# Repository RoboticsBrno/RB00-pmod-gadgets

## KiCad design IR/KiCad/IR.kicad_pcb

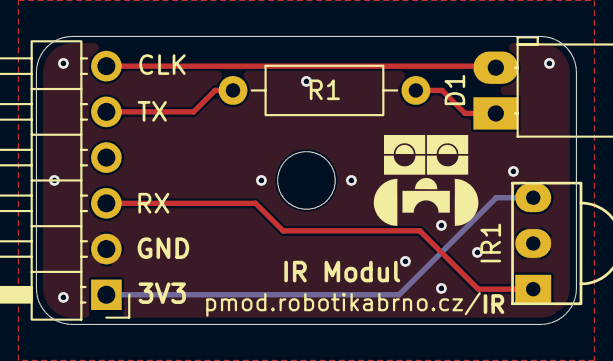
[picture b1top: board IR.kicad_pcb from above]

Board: 2 copper layers, 30.0 x 16.0 mm, 5 parts (0 on the bottom side), 6 nets.

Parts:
D1: IR; LED_D5.0mm_Horizontal_O1.27mm_Z3.0mm_IRBlack
IR1: VS1838b
J1: Conn_01x06; PinHeader_1x06_P2.54mm_Horizontal
M3: MountingHole_3.2mm_M3
R1: 100; R_Axial_DIN0207_L6.3mm_D2.5mm_P10.16mm_Horizontal

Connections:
+3.3V: IR1.3 (VCC), J1.1
CLK: D1.2 (A), J1.6
GND: IR1.2 (GND), J1.2
unnamed: D1.1 (K), R1.2
RX: IR1.1 (OUT), J1.3
TX: J1.5, R1.1

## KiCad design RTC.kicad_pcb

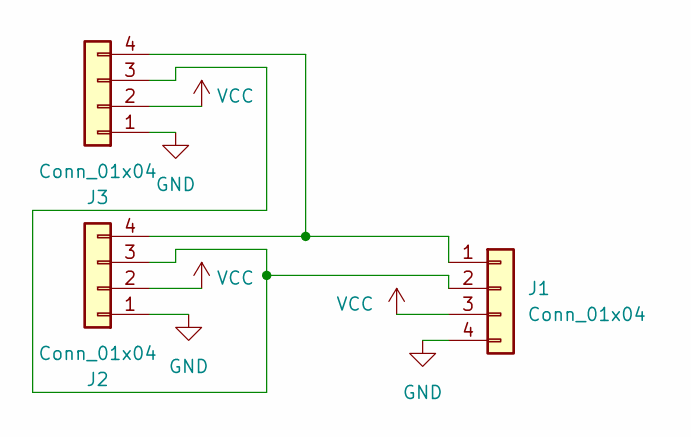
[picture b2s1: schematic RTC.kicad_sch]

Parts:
J1: Conn_01x04; PinHeader_1x04_P2.54mm_Vertical
J2, J3: Conn_01x04; JST_SH_BM04B-SRSS-TB_1x04-1MP_P1.00mm_Vertical

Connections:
GND: J1.4, J2.1, J3.1
unnamed: J1.1, J2.4, J3.4
unnamed: J1.2, J2.3, J3.3
VCC: J1.3, J2.2, J3.2

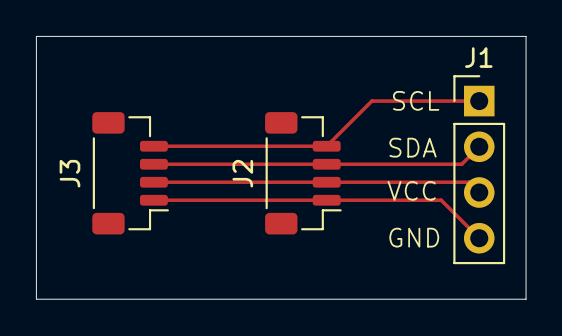
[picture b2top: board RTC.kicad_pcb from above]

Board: 2 copper layers, 27.2 x 14.6 mm, 3 parts (0 on the bottom side), 4 nets.

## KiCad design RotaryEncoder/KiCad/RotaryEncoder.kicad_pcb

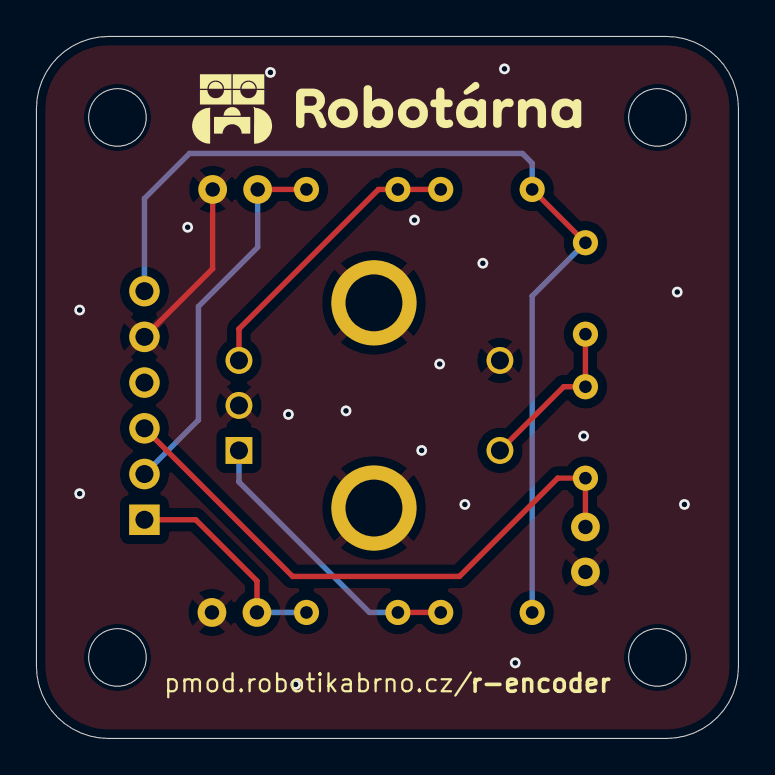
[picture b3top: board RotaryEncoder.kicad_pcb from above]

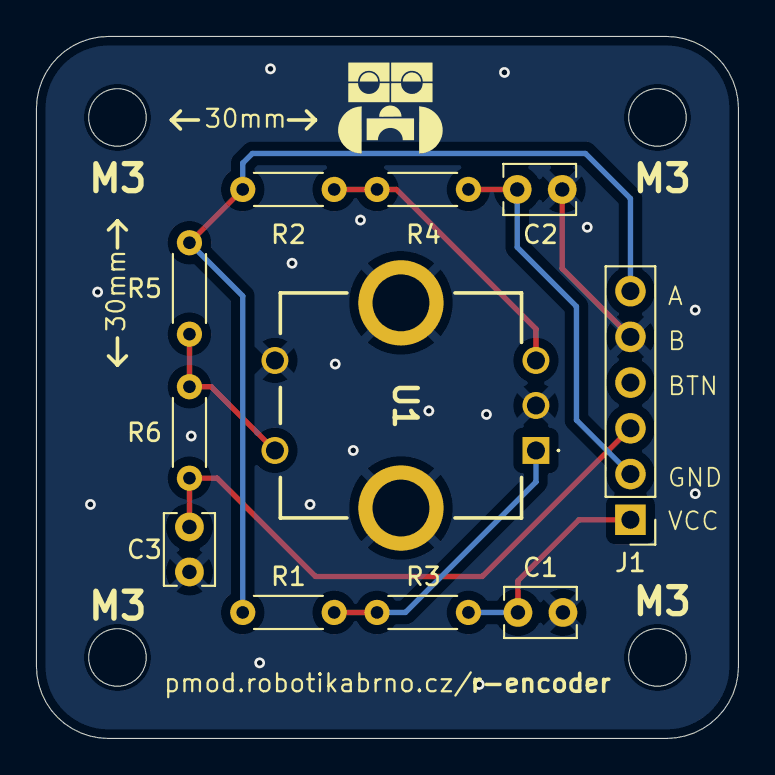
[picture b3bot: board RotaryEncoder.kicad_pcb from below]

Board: 2 copper layers, 39.0 x 39.0 mm, 15 parts (11 on the bottom side), 8 nets.

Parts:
C1, C2, C3: 0.01uF; C_Disc_D3.8mm_W2.6mm_P2.50mm
H1, H2, H3, H4: MountingHole; MountingHole_3.2mm_M3
J1: Conn_01x06; PinHeader_1x06_P2.54mm_Vertical
R1, R2, R3, R4, R5, R6: 10K; R_Axial_DIN0204_L3.6mm_D1.6mm_P5.08mm_Horizontal
U1: PEC11R-4325F-S0012; PEC11R4325FS0012

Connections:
A: C1.2, J1.1, R3.2
B: C2.2, J1.2, R4.1
BTN: C3.1, J1.3, R6.2
GND: C1.1, C2.1, C3.2, J1.5, U1.2 (NO), U1.3 (MH1), U1.4 (MH2), U1.C1 (C_COMMON)
unnamed: R1.2, R3.1, U1.A1 (A_CHANNEL)
unnamed: R2.2, R4.2, U1.B1 (B_CHANNEL)
unnamed: R5.1, R6.1, U1.1 (COM)
VCC: J1.6, R1.1, R2.1, R5.2

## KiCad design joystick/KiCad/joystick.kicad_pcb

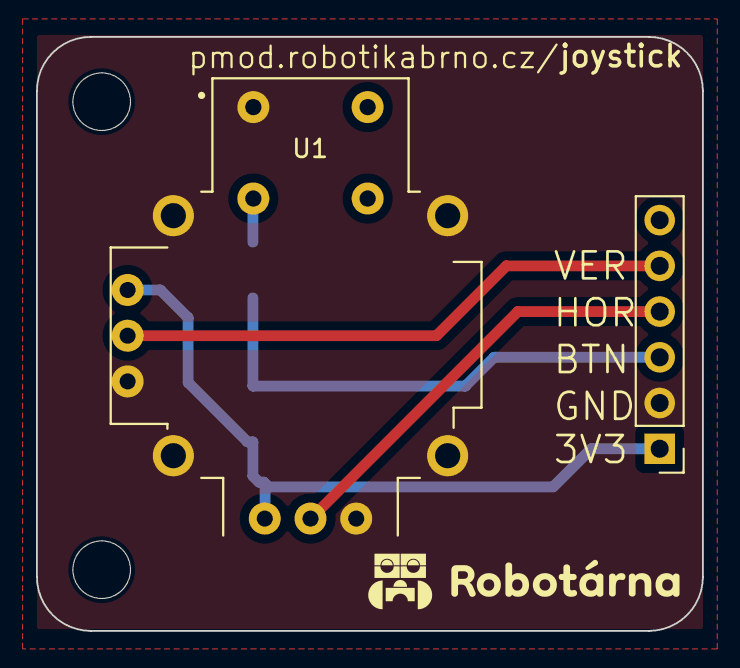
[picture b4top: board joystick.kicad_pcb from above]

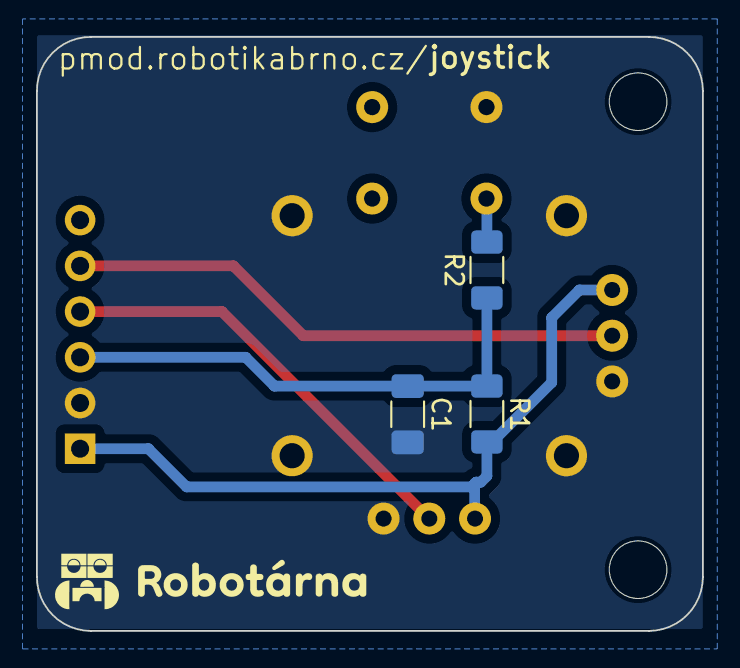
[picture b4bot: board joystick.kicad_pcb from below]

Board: 2 copper layers, 37.0 x 33.0 mm, 7 parts (3 on the bottom side), 6 nets.

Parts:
C1: 0.1uF; C_1206_3216Metric_Pad1.33x1.80mm_HandSolder
H1, H2: MountingHole; MountingHole_3.2mm_M3_DIN965
J1: Conn_01x06_Pin; PinHeader_1x06_P2.54mm_Vertical
R1: 10k; R_1206_3216Metric_Pad1.30x1.75mm_HandSolder
R2: 1k; R_1206_3216Metric_Pad1.30x1.75mm_HandSolder
U1: COM-09032; XDCR_COM-09032

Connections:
/3V3: J1.1, R1.2, U1.H1 (H+), U1.V1 (V+)
/GND: C1.2, J1.2, U1.B1A (SEL+), U1.H3 (H-), U1.S1 (SHIELD), U1.S2 (SHIELD), U1.S3 (SHIELD), U1.S4 (SHIELD), U1.V3 (V-)
/H: J1.4, U1.H2 (H)
/SEL: C1.1, J1.3, R1.1, R2.1
/V: J1.5, U1.V2 (V)
unnamed: R2.2, U1.B2A (SEL-)

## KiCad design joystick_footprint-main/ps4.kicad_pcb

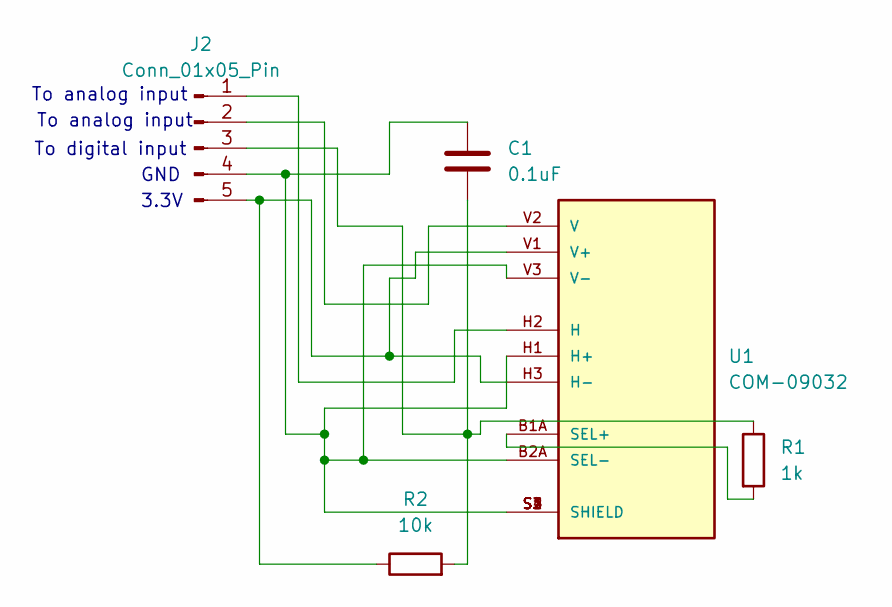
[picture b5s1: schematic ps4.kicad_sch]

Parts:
C1: 0.1uF; C_0603_1608Metric
J2: Conn_01x05_Pin; PinHeader_1x05_P2.54mm_Vertical
R1: 1k; R_0603_1608Metric_Pad0.98x0.95mm_HandSolder
R2: 10k; R_0603_1608Metric_Pad0.98x0.95mm_HandSolder
U1: COM-09032; XDCR_COM-09032; PARTREV N/A

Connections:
unnamed: J2.1, U1.H2 (H)
unnamed: J2.2, U1.V2 (V)
unnamed: C1.2, J2.3, R1.1, R2.2
unnamed: C1.1, J2.4, U1.B2A (SEL-), U1.H1 (H+), U1.S1 (SHIELD), U1.S2 (SHIELD), U1.S3 (SHIELD), U1.S4 (SHIELD), U1.V3 (V-)
unnamed: J2.5, R2.1, U1.H3 (H-), U1.V1 (V+)
unnamed: R1.2, U1.B1A (SEL+)

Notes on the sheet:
3.3V
To digital input
To analog input
GND

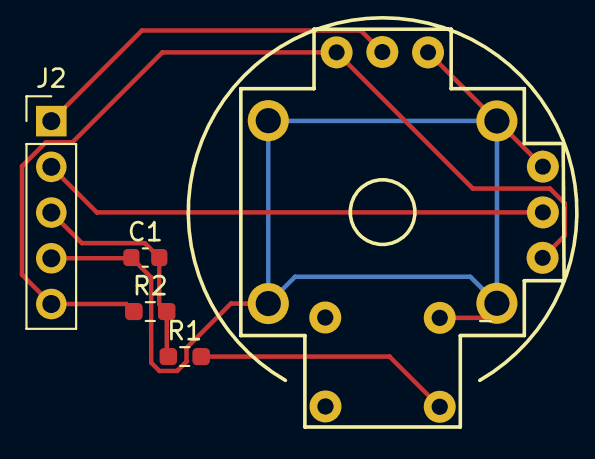
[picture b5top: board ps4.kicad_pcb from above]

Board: 2 copper layers, 5 parts (0 on the bottom side), 6 nets.

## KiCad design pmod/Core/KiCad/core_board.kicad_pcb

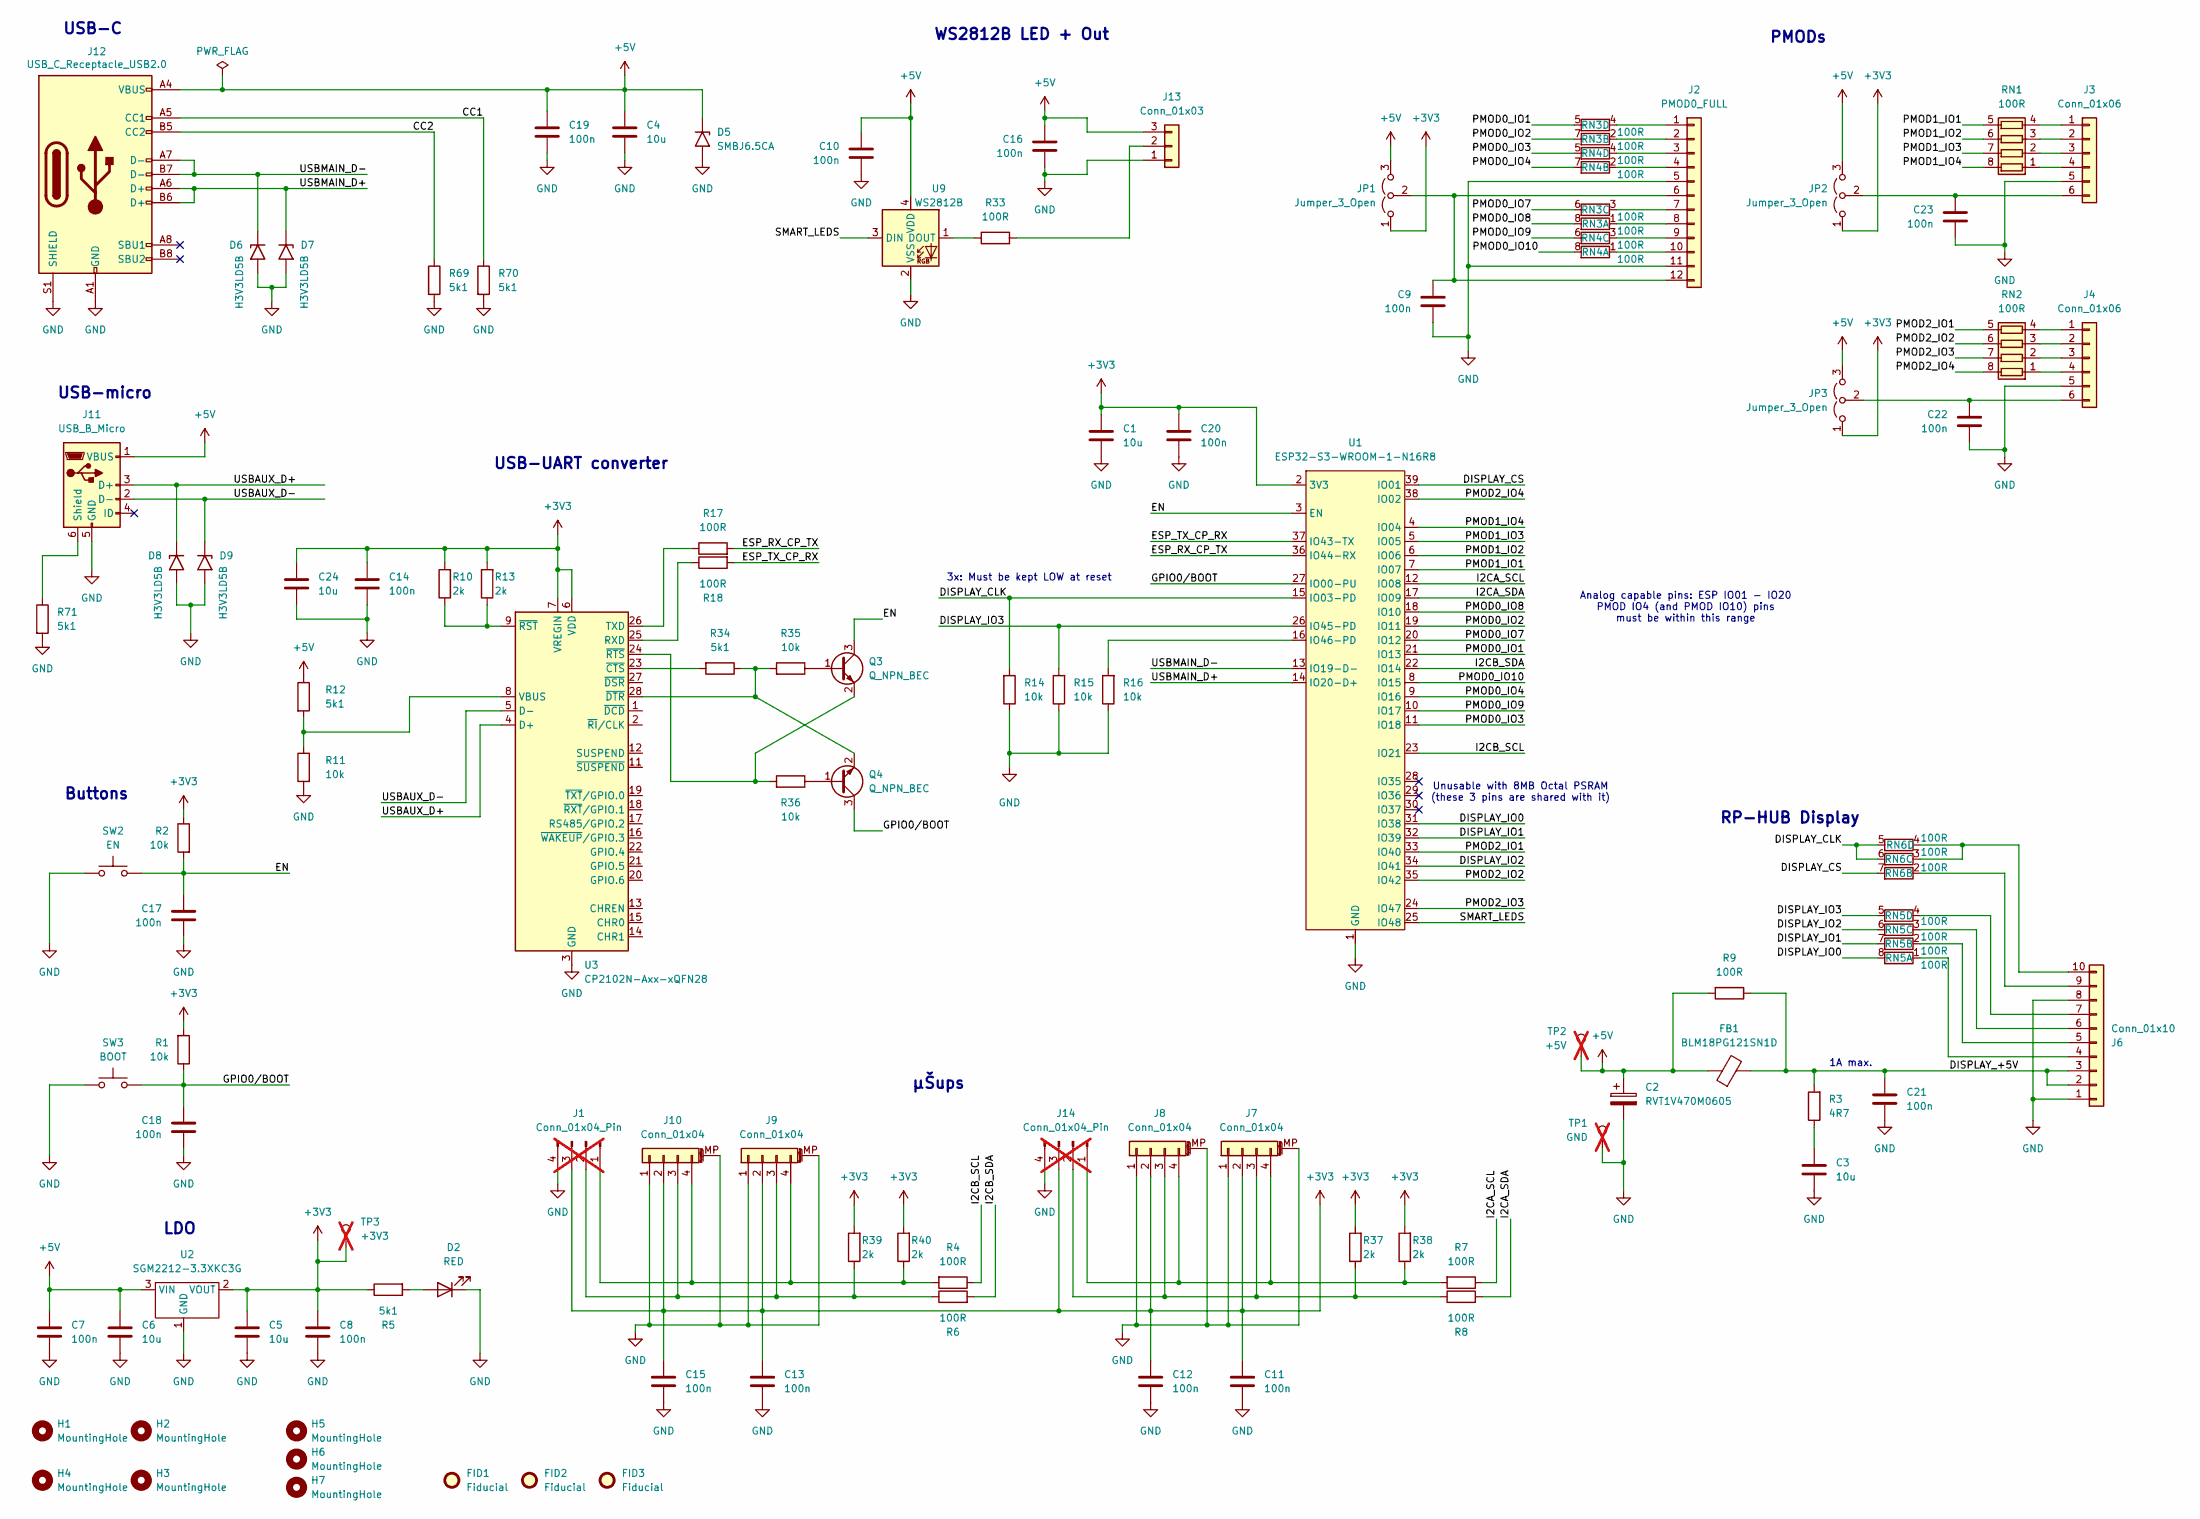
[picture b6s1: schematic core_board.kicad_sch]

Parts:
C1, C3, C4, C5, C6, C24: 10u; C_1206_3216Metric; LCSC C13585
C2: RVT1V470M0605; CP_Elec_6.3x5.4; LCSC C72522
C7, C8, C9, C10, C11, C12, C13, C14, C15, C16, C17, C18, C19, C20, C21, C22, C23: 100n; C_0402_1005Metric; LCSC C307331
D2: RED; LED_0603_1608Metric; LCSC C965799
D5: SMBJ6.5CA; D_SMB; LCSC C7420377
D6, D7, D8, D9: H3V3LD5B; D_SOD-523; LCSC C20615817
FB1: BLM18PG121SN1D; L_0603_1608Metric; LCSC C14709
FID1, FID2, FID3: Fiducial; Fiducial_1mm_Mask2mm
H1, H2, H3, H4: MountingHole; MountingHole_3.2mm_M3_DIN965
H5, H6, H7: MountingHole; ToolingHole_1.152mm
J1, J14: Conn_01x04_Pin; PinSocket_1x04_P2.54mm_Vertical; not fitted
J2: PMOD0_FULL; PinSocket_PMOD_full; LCSC C2897426
J3, J4: Conn_01x06; PinSocket_PMOD_Half; LCSC C2897388
J6: Conn_01x10; JST_XH_S10B-XH-A-1_1x10_P2.50mm_Horizontal; LCSC C491718
J7, J8, J9, J10: Conn_01x04; JST_SH_SM04B-SRSS-TB_1x04-1MP_P1.00mm_Horizontal; LCSC C7430446
J11: USB_B_Micro; USB_Micro-B_Molex-105017-0001; LCSC C404969
J12: USB_C_Receptacle_USB2.0; USB_C_Receptacle_HRO_TYPE-C-31-M-12; LCSC C165948
J13: Conn_01x03; JST_XH_S3B-XH-A-1_1x03_P2.50mm_Horizontal; LCSC C493416
JP1, JP2, JP3: Jumper_3_Open; PinHeader_1x03_P2.54mm_Vertical; LCSC C49257
Q3, Q4: Q_NPN_BEC; SOT-23; LCSC C20526
R1, R2, R11, R14, R15, R16, R35, R36: 10k; R_0402_1005Metric; LCSC C25744
R3: 4R7; R_0805_2012Metric; LCSC C17675
R4, R6, R7, R8, R9, R17, R18, R33: 100R; R_0402_1005Metric; LCSC C25076
R5, R12, R34, R69, R70, R71: 5k1; R_0402_1005Metric; LCSC C25905
R10, R13, R37, R38, R39, R40: 2k; R_0402_1005Metric; LCSC C4109
RN1, RN2, RN3, RN4, RN5, RN6: 100R; R_Array_Convex_4x0603; LCSC C25506
SW2: EN; SW_Push_1P1T_NO_Vertical_Wuerth_434133025816; LCSC C115360
SW3: BOOT; SW_Push_1P1T_NO_Vertical_Wuerth_434133025816; LCSC C115360
TP1: GND; PinHeader_1x01_P2.54mm_Vertical; not fitted
TP2: +5V; PinHeader_1x01_P2.54mm_Vertical; not fitted
TP3: +3V3; PinHeader_1x01_P2.54mm_Vertical; not fitted
U1: ESP32-S3-WROOM-1-N16R8; ESP32-S3-WROOM; LCSC C2913202
U2: SGM2212-3.3XKC3G; SOT-223-3_TabPin2; LCSC C3294699
U3: CP2102N-Axx-xQFN28; QFN-28-1EP_5x5mm_P0.5mm_EP3.35x3.35mm; LCSC C964632
U9: WS2812B; LED_WS2812B-2020_PLCC4_2.0x2.0mm; LCSC C5349955

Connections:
+3V3: C1.1, C5.1, C8.1, C11.1, C12.1, C13.1, C14.1, C15.1, C20.1, C24.1, J1.3, J7.2, J8.2, J9.2, J10.2, J14.3, JP1.1 (A), JP2.1 (A), JP3.1 (A), R1.2, R2.1, R5.1, R10.2, R13.2, R37.2, R38.2, R39.2, R40.2, TP3.1, U1.2 (3V3), U2.2 (VOUT), U3.6 (VDD), U3.7 (VREGIN)
+5V: C2.1, C4.1, C6.1, C7.1, C10.1, C16.1, C19.1, D5.1 (A1), FB1.1, J11.1 (VBUS), J12.A4 (VBUS), J12.A9 (VBUS), J12.B4 (VBUS), J12.B9 (VBUS), J13.3, JP1.3 (B), JP2.3 (B), JP3.3 (B), R9.2, R12.1, TP2.1, U2.3 (VIN), U9.4 (VDD)
/CC1: J12.A5 (CC1), R70.1
/CC2: J12.B5 (CC2), R69.1
/DISPLAY_+5V: C21.1, FB1.2, J6.2, J6.3, R3.2, R9.1
/DISPLAY_CLK: R14.2, RN6.5 (R4.2), RN6.6 (R3.2), U1.15 (IO03-PD)
/DISPLAY_CS: RN6.7 (R2.2), U1.39 (IO01)
/DISPLAY_IO0: RN5.8 (R1.2), U1.31 (IO38)
/DISPLAY_IO1: RN5.7 (R2.2), U1.32 (IO39)
/DISPLAY_IO2: RN5.6 (R3.2), U1.34 (IO41)
/DISPLAY_IO3: R15.2, RN5.5 (R4.2), U1.26 (IO45-PD)
/EN: C17.1, Q3.3 (C), R2.2, SW2.1, U1.3 (EN)
/ESP_RX_CP_TX: R17.2, U1.36 (IO44-RX)
/ESP_TX_CP_RX: R18.2, U1.37 (IO43-TX)
/GPIO0/BOOT: C18.1, Q4.3 (C), R1.1, SW3.1, U1.27 (IO00-PU)
/I2CA_SCL: R7.1, U1.12 (IO08)
/I2CA_SDA: R8.2, U1.17 (IO09)
/I2CB_SCL: R4.1, U1.23 (IO21)
/I2CB_SDA: R6.2, U1.22 (IO14)
/PMOD0_IO1: RN3.5 (R4.2), U1.21 (IO13)
/PMOD0_IO2: RN3.7 (R2.2), U1.19 (IO11)
/PMOD0_IO3: RN4.5 (R4.2), U1.11 (IO18)
/PMOD0_IO4: RN4.7 (R2.2), U1.9 (IO16)
/PMOD0_IO7: RN3.6 (R3.2), U1.20 (IO12)
/PMOD0_IO8: RN3.8 (R1.2), U1.18 (IO10)
/PMOD0_IO9: RN4.6 (R3.2), U1.10 (IO17)
/PMOD0_IO10: RN4.8 (R1.2), U1.8 (IO15)
/PMOD1_IO1: RN1.5 (R4.2), U1.7 (IO07)
/PMOD1_IO2: RN1.6 (R3.2), U1.6 (IO06)
/PMOD1_IO3: RN1.7 (R2.2), U1.5 (IO05)
/PMOD1_IO4: RN1.8 (R1.2), U1.4 (IO04)
/PMOD2_IO1: RN2.5 (R4.2), U1.33 (IO40)
/PMOD2_IO2: RN2.6 (R3.2), U1.35 (IO42)
/PMOD2_IO3: RN2.7 (R2.2), U1.24 (IO47)
/PMOD2_IO4: RN2.8 (R1.2), U1.38 (IO02)
/SMART_LEDS: U1.25 (IO48), U9.3 (DIN)
/USBAUX_D+: D8.1 (A1), J11.3 (D+), U3.4 (D+)
/USBAUX_D-: D9.1 (A1), J11.2 (D-), U3.5 (D-)
/USBMAIN_D+: D7.1 (A1), J12.A6 (D+), J12.B6 (D+), U1.14 (IO20-D+)
/USBMAIN_D-: D6.1 (A1), J12.A7 (D-), J12.B7 (D-), U1.13 (IO19-D-)
GND: C1.2, C2.2, C3.2, C4.2, C5.2, C6.2, C7.2, C8.2, C9.2, C10.2, C11.2, C12.2, C13.2, C14.2, C15.2, C16.2, C17.2, C18.2, C19.2, C20.2, C21.2, C22.2, C23.2, C24.2, D2.1 (K), D5.2 (A2), D6.2 (A2), D7.2 (A2), D8.2 (A2), D9.2 (A2), J1.4, J2.5, J2.11, J3.5, J4.5, J6.1, J6.8, J7.1, J7.MP (MountPin), J8.1, J8.MP (MountPin), J9.1, J9.MP (MountPin), J10.1, J10.MP (MountPin), J11.5 (GND), J12.A1 (GND), J12.A12 (GND), J12.B1 (GND), J12.B12 (GND), J12.S1 (SHIELD), J13.1, J14.4, R11.2, R14.1, R15.1, R16.1, R69.2, R70.2, R71.2, SW2.2, SW3.2, TP1.1, U1.1 (GND), U1.40 (GND), U1.41 (GND), U2.1 (GND), U3.3 (GND), U3.29 (GND), U9.2 (VSS)
unnamed: C3.1, R3.1
unnamed: D2.2 (A), R5.2
unnamed: J1.1, J9.4, J10.4, R4.2, R40.1
unnamed: J1.2, J9.3, J10.3, R6.1, R39.1
unnamed: J2.1, RN3.4 (R4.1)
unnamed: J2.2, RN3.2 (R2.1)
unnamed: J2.3, RN4.4 (R4.1)
unnamed: J2.4, RN4.2 (R2.1)
unnamed: J2.7, RN3.3 (R3.1)
unnamed: J2.8, RN3.1 (R1.1)
unnamed: J2.9, RN4.3 (R3.1)
unnamed: J2.10, RN4.1 (R1.1)
unnamed: C9.1, J2.6, J2.12, JP1.2 (C)
unnamed: J3.1, RN1.4 (R4.1)
unnamed: J3.2, RN1.3 (R3.1)
unnamed: J3.3, RN1.2 (R2.1)
unnamed: J3.4, RN1.1 (R1.1)
unnamed: C23.1, J3.6, JP2.2 (C)
unnamed: J4.1, RN2.4 (R4.1)
unnamed: J4.2, RN2.3 (R3.1)
unnamed: J4.3, RN2.2 (R2.1)
unnamed: J4.4, RN2.1 (R1.1)
unnamed: C22.1, J4.6, JP3.2 (C)
unnamed: J6.4, RN5.1 (R1.1)
unnamed: J6.5, RN5.2 (R2.1)
unnamed: J6.6, RN5.3 (R3.1)
unnamed: J6.7, RN5.4 (R4.1)
unnamed: J6.9, RN6.2 (R2.1)
unnamed: J6.10, RN6.3 (R3.1), RN6.4 (R4.1)
unnamed: J11.6 (Shield), R71.1
unnamed: J13.2, R33.2
unnamed: J7.4, J8.4, J14.1, R7.2, R38.1
unnamed: J7.3, J8.3, J14.2, R8.1, R37.1
unnamed: Q3.1 (B), R35.1
unnamed: Q3.2 (E), R36.2, U3.24 (~RTS)
unnamed: Q4.1 (B), R36.1
unnamed: Q4.2 (E), R34.1, R35.2, U3.28 (~DTR)
unnamed: R16.2, U1.16 (IO46-PD)
unnamed: R18.1, U3.25 (RXD)
unnamed: R17.1, U3.26 (TXD)
unnamed: R11.1, R12.2, U3.8 (VBUS)
unnamed: R34.2, U3.23 (~CTS)
unnamed: R10.1, R13.1, U3.9 (~RST)
unnamed: R33.1, U9.1 (DOUT)

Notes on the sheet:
USB-UART converter
Unusable with 8MB Octal PSRAM (these 3 pins are shared with it)
3x: Must be kept LOW at reset
1A max.
RP-HUB Display
µŠups
PMODs
USB-micro
WS2812B LED + Out
USB-C
LDO
Buttons
Analog capable pins: ESP IO01 - IO20 PMOD IO4 (and PMOD IO10) pins must be within this range

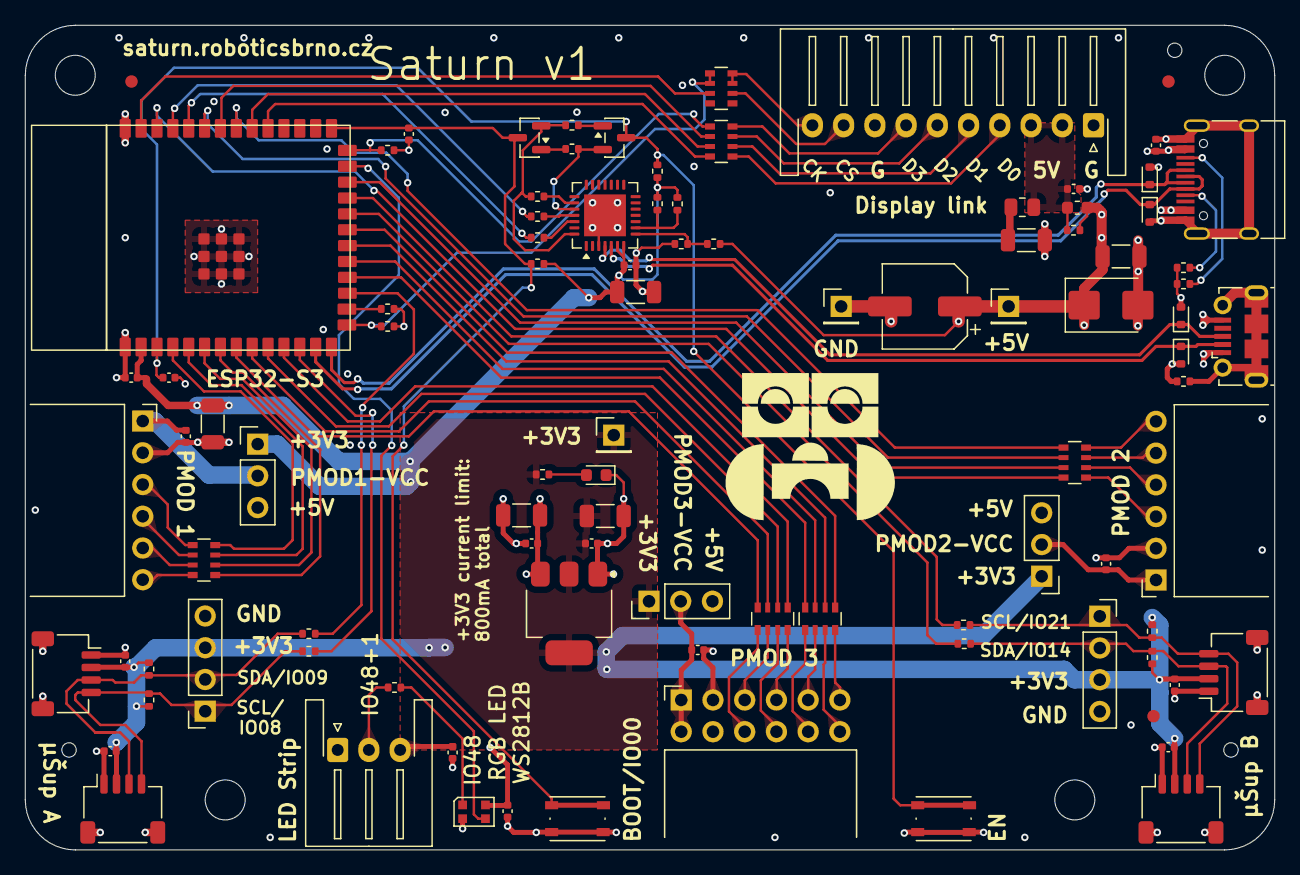
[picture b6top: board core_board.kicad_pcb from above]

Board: 4 copper layers, 100.0 x 66.0 mm, 103 parts (0 on the bottom side), 85 nets.

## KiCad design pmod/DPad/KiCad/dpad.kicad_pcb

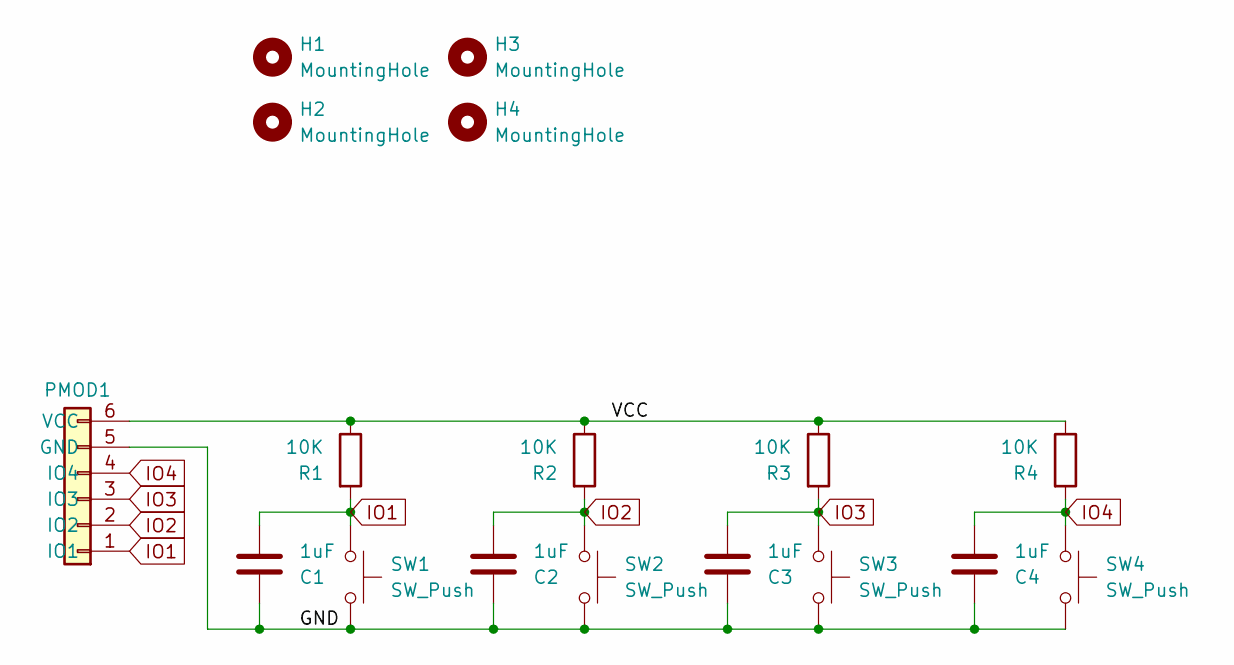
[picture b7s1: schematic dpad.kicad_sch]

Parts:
C1, C2, C3, C4: 1uF; C_Disc_D6.0mm_W4mm_P5.00mm
H1, H2, H3, H4: MountingHole; MountingHole_3.2mm_M3
PMOD1: Conn_01x06; PinHeader_1x06_P2.54mm_Horizontal
R1, R2, R3, R4: 10K; R_Axial_DIN0204_L3.6mm_D1.6mm_P5.08mm_Horizontal
SW1, SW2, SW3, SW4: SW_Push; SW_PUSH-12mm

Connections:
/GND: C1.1, C2.1, C3.1, C4.1, PMOD1.5 (GND), SW1.2, SW2.2, SW3.2, SW4.2
/VCC: PMOD1.6 (VCC), R1.1, R2.1, R3.1, R4.1
IO1: C1.2, PMOD1.1 (IO1), R1.2, SW1.1
IO2: C2.2, PMOD1.2 (IO2), R2.2, SW2.1
IO3: C3.2, PMOD1.3 (IO3), R3.2, SW3.1
IO4: C4.2, PMOD1.4 (IO4), R4.2, SW4.1

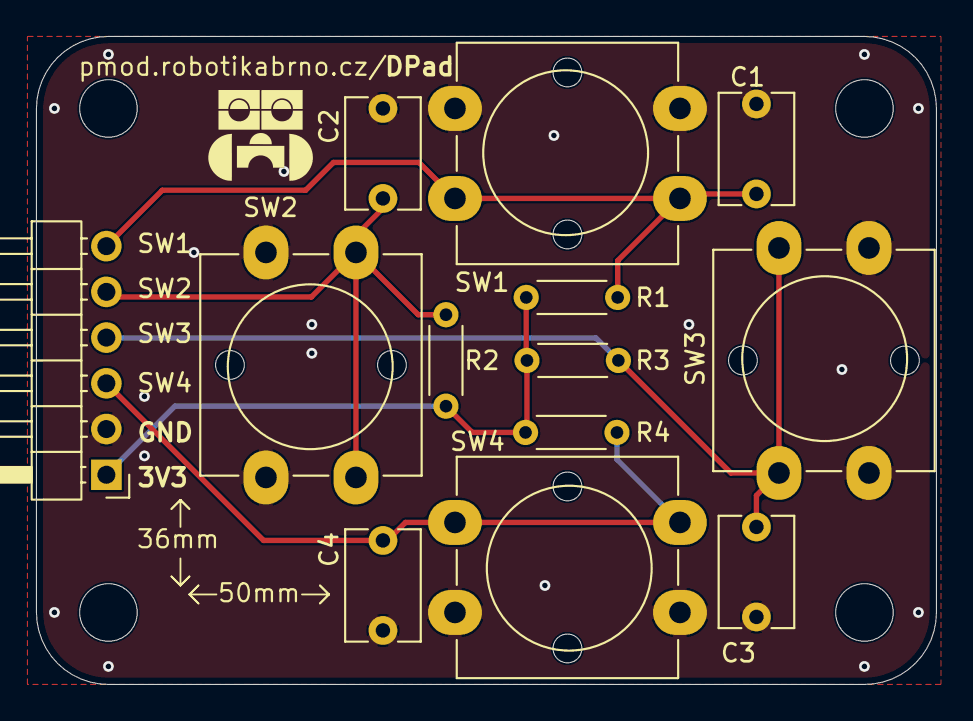
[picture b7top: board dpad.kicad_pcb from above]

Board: 2 copper layers, 50.0 x 36.0 mm, 17 parts (0 on the bottom side), 6 nets.
